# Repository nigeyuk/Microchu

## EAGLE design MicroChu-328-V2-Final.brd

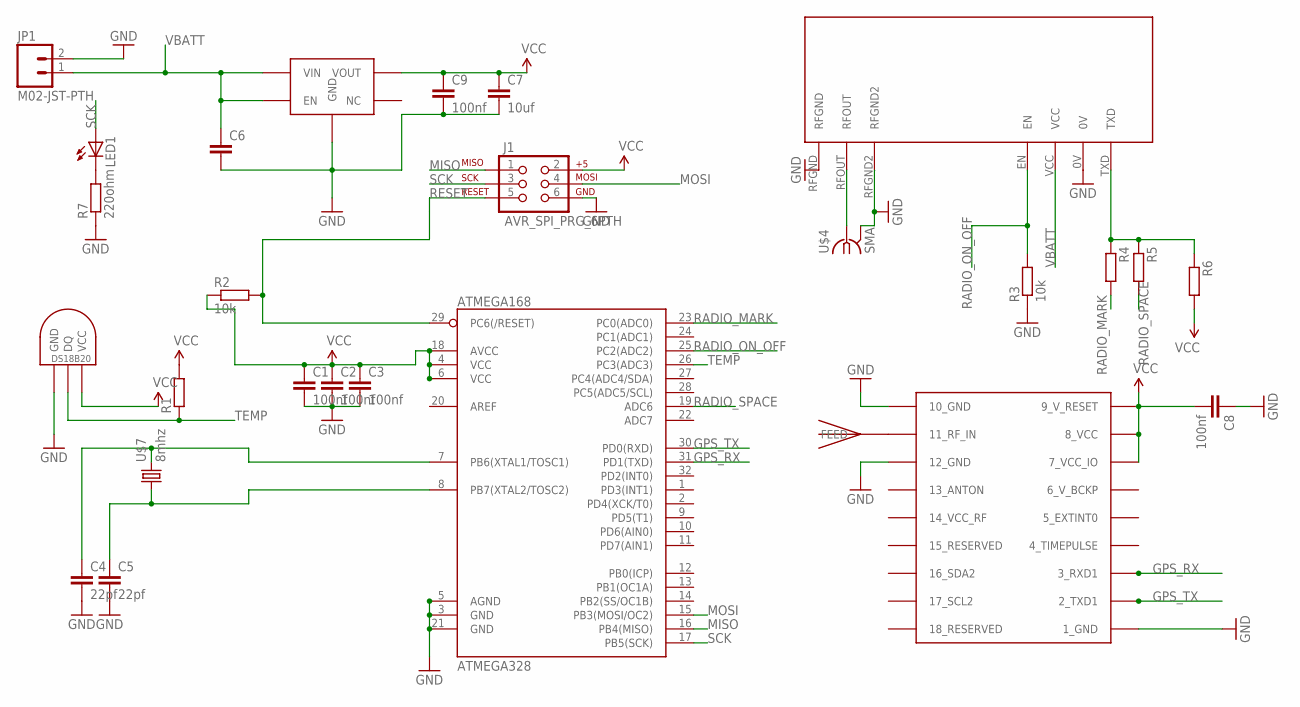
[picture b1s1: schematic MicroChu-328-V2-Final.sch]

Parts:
3V3: ADP122AUJZ-3V3REG-5TSOT; SOT23-5L
ATMEGA328: ATMEGA168; TQFP32-08
C1, C2, C3, C8, C9: 100nf; C0805
C4, C5: 22pf; C0805
C6: C-EUC0805; C0805
C7: 10uf; C0805
J1: AVR_SPI_PRG_6PTH; 2X3
JP1: M02-JST-PTH
LED1: LED1206; LED-1206
R1, R4, R5, R6: R-EU_R0805; R0805
R2, R3: 10k; R0805
R7: 220ohm; R0805
U$1: JTI_ANTENNA-1575AT43A40
U$2: NTX2
U$3: UBLOX_MAX-6
U$4: SMA; BU-SMA-H
U$6: DS1820TO92; DS1820
U$7: 8mhz; ABRACON_ABM3_CRYSTAL

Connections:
GND: 3V3.2 (GND), ATMEGA328.3 (GND), ATMEGA328.5 (AGND), ATMEGA328.21 (GND), C1.2, C2.2, C3.2, C4.2, C5.2, C6.2, C7.2, C8.1, C9.2, J1.6, JP1.2, R3.1, R7.1, U$2.0V, U$2.RFGND, U$2.RFGND2, U$3.1_GND, U$3.10_GND, U$3.12_GND, U$4.2 (GND), U$4.3 (GND), U$4.4 (GND), U$4.5 (GND), U$6.GND
GPS_RX: ATMEGA328.31 (PD1(TXD)), U$3.3_RXD1
GPS_TX: ATMEGA328.30 (PD0(RXD)), U$3.2_TXD1
MISO: ATMEGA328.16 (PB4(MISO)), J1.1
MOSI: ATMEGA328.15 (PB3(MOSI/OC2)), J1.4
unnamed: ATMEGA328.7 (PB6(XTAL1/TOSC1)), C4.1, U$7.P$2 (2)
unnamed: LED1.C, R7.2
unnamed: ATMEGA328.8 (PB7(XTAL2/TOSC2)), C5.1, U$7.P$1 (1)
unnamed: U$1.FEED, U$3.11_RF_IN
unnamed: R4.1, R5.1, R6.1, U$2.TXD
unnamed: U$2.RFOUT, U$4.1
RADIO_MARK: ATMEGA328.23 (PC0(ADC0)), R4.2
RADIO_ON_OFF: ATMEGA328.25 (PC2(ADC2)), R3.2, U$2.EN
RADIO_SPACE: ATMEGA328.19 (ADC6), R5.2
RESET: ATMEGA328.29 (PC6(/RESET)), J1.5, R2.2
SCK: ATMEGA328.17 (PB5(SCK)), J1.3, LED1.A
TEMP: ATMEGA328.26 (PC3(ADC3)), R1.1, U$6.DQ
VBATT: 3V3.1 (VIN), 3V3.3 (EN), C6.1, JP1.1, U$2.VCC
VCC: 3V3.5 (VOUT), ATMEGA328.4 (VCC), ATMEGA328.6 (VCC), ATMEGA328.18 (AVCC), C1.1, C2.1, C3.1, C7.1, C8.2, C9.1, J1.2, R1.2, R2.1, R6.2, U$3.7_VCC_IO, U$3.8_VCC, U$3.9_V_RESET, U$6.VDD (VCC)

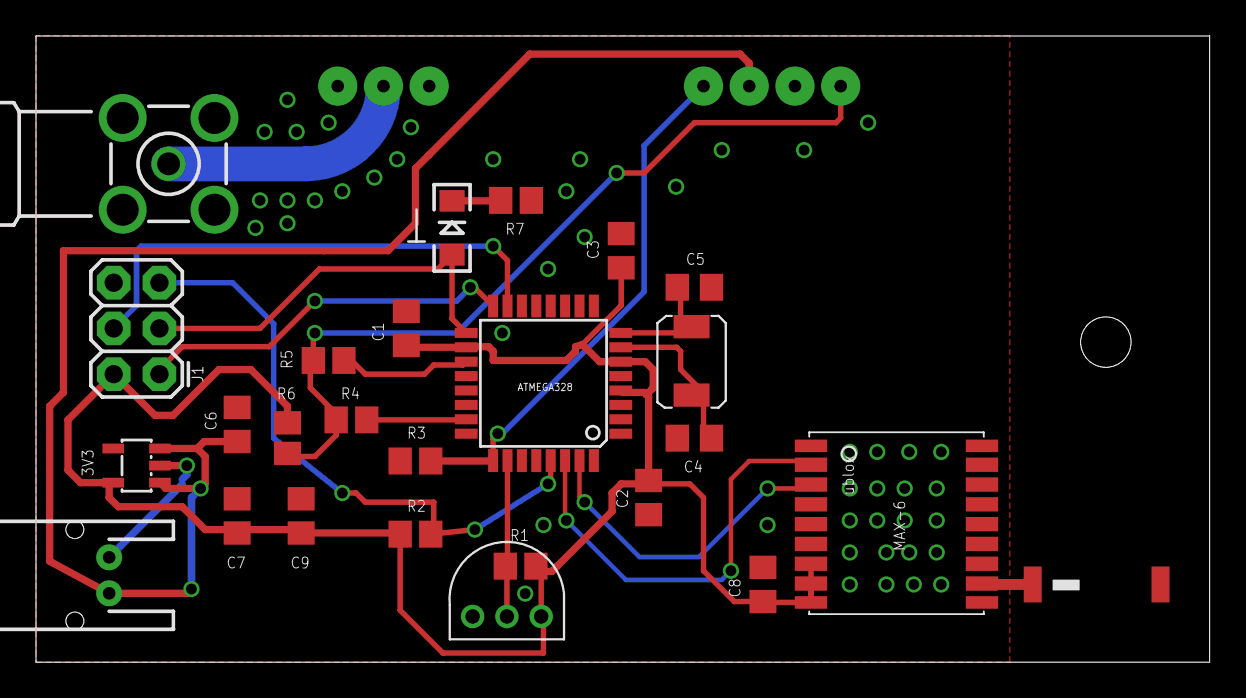
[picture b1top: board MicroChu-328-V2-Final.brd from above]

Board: 2 copper layers, 65.2 x 34.8 mm, 27 parts (1 on the bottom side), 19 nets.

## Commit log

2013-02-24 Included PINS Definition
2013-02-24 Update gps to use swift stable version
2013-02-24 Fixed incorrect crccat value causing checksums to fail
2013-02-24 added a TODO
2013-02-26 included schematics and board files
2013-02-28 more fixes
2013-03-06 minor changes to microchu.c set config for 300baud
2013-03-08 First attempts at powersaving
2013-03-10 More powersaving features, thanks Phil!
2013-03-11 changed location of psm, fixes psm read errors

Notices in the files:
parts and their libraries:
SparkFun: Licensing: CC v3.0 Share-Alike You are welcome to use this library for commercial purposes.
